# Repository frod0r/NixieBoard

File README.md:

Here I try to recreate the schematics and layout of the nixie clock from this nice instrucables creator:
http://www.instructables.com/id/simple-user-adjustable-DIY-Nixie-Clock/

Please note that I am done BUT I built the clock and it does not work. I have not figured out if it is the components or my plans. I will try to debug it and update here as soon as it works

The reason for me doing so is so that I can generate gerber files with wich I or you can easily order the pcb istead of echtching it oneself :)
If you Andrea Biffi (The creator of the original plans on wich I base my on) want me to remove this respority for a reason, please contact me and I 
will do so.

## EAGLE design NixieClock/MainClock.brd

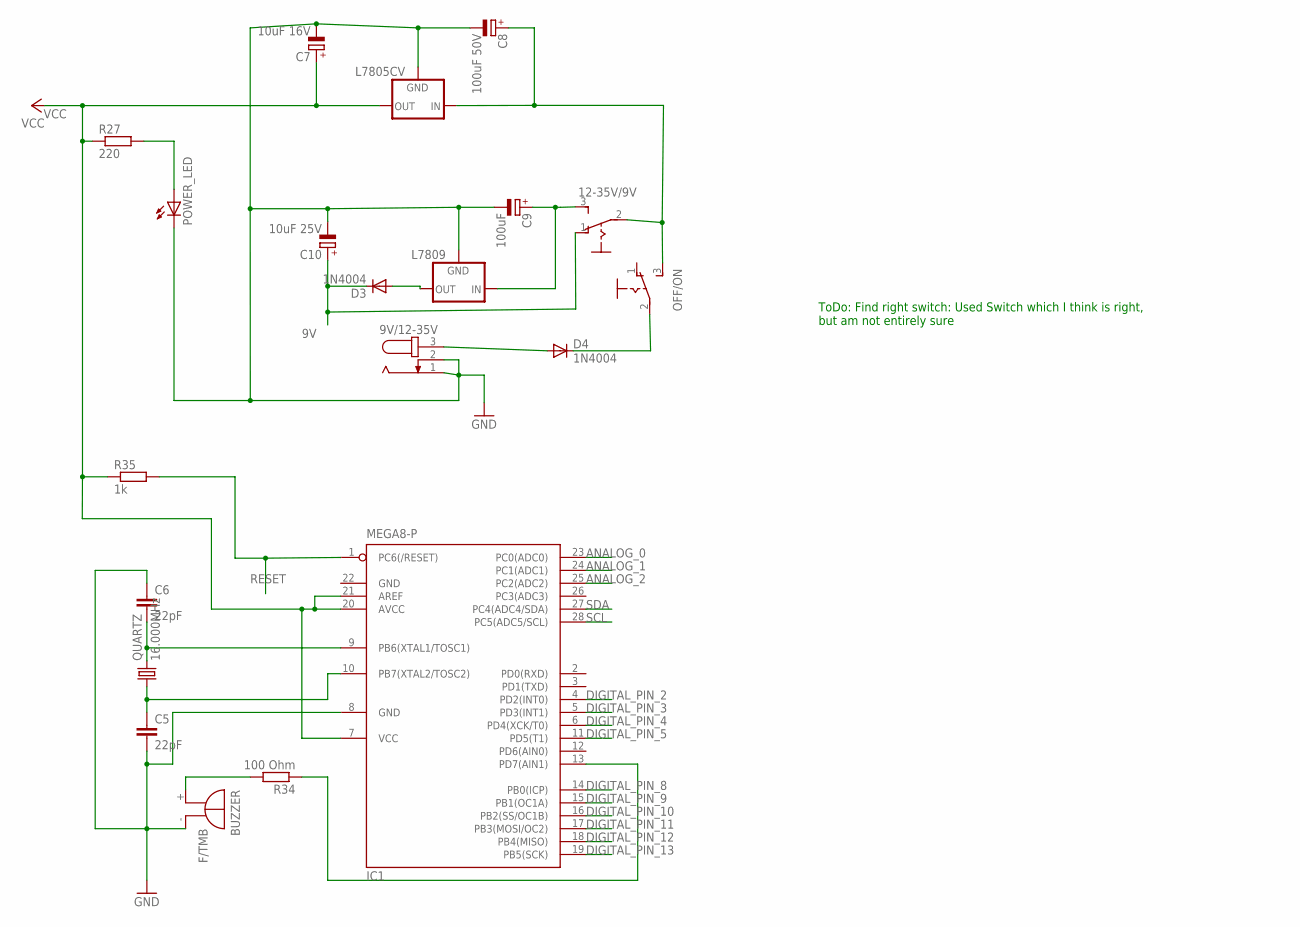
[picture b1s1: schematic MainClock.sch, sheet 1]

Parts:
9V/12-35V: JACK-PLUG1; SPC4078
12-35V/9V: 255SB
BUZZER: F/TMB
C5, C6: 22pF; C025-025X050
C7: 10uF 16V; E5-6
C8: 100uF 50V; E5-8,5
C9: 100uF; E5-8,5
C10: 10uF 25V; E5-6
D3, D4: 1N4004; DO41-10
IC1: MEGA8-P; DIL28-3
L7805CV, L7809: 78XXS
OFF/ON: 255SB
POWER_LED: LED5MM
QUARTZ: 16.000MHz; HC49/S
R27: 220; 0309/10
R34: 100 Ohm; 0411/15
R35: 1k; 0309/10

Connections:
9V: 12-35V/9V.1 (O), C10.+, D3.C; also elsewhere on the board
ANALOG_0: IC1.23 (PC0(ADC0)); also elsewhere on the board
ANALOG_1: IC1.24 (PC1(ADC1)); also elsewhere on the board
ANALOG_2: IC1.25 (PC2(ADC2)); also elsewhere on the board
DIGITAL_PIN_2: IC1.4 (PD2(INT0)); also elsewhere on the board
DIGITAL_PIN_3: IC1.5 (PD3(INT1)); also elsewhere on the board
DIGITAL_PIN_4: IC1.6 (PD4(XCK/T0)); also elsewhere on the board
DIGITAL_PIN_5: IC1.11 (PD5(T1)); also elsewhere on the board
DIGITAL_PIN_8: IC1.14 (PB0(ICP)); also elsewhere on the board
DIGITAL_PIN_9: IC1.15 (PB1(OC1A)); also elsewhere on the board
DIGITAL_PIN_10: IC1.16 (PB2(SS/OC1B)); also elsewhere on the board
DIGITAL_PIN_11: IC1.17 (PB3(MOSI/OC2)); also elsewhere on the board
DIGITAL_PIN_12: IC1.18 (PB4(MISO)); also elsewhere on the board
DIGITAL_PIN_13: IC1.19 (PB5(SCK)); also elsewhere on the board
GND: 9V/12-35V.1, 9V/12-35V.2, BUZZER.-, C5.2, C6.1, C7.-, C8.-, C9.-, C10.-, IC1.8 (GND), IC1.22 (GND), L7805CV.GND, L7809.GND, POWER_LED.K (C); also elsewhere on the board
unnamed: C6.2, IC1.9 (PB6(XTAL1/TOSC1)), QUARTZ.2
unnamed: C5.1, IC1.10 (PB7(XTAL2/TOSC2)), QUARTZ.1
unnamed: BUZZER.+, R34.2
unnamed: IC1.13 (PD7(AIN1)), R34.1
unnamed: 9V/12-35V.3, D4.A
unnamed: D4.C, OFF/ON.2
unnamed: 12-35V/9V.2, C8.+, L7805CV.IN, OFF/ON.3 (S)
unnamed: 12-35V/9V.3 (S), C9.+, L7809.IN
unnamed: POWER_LED.A, R27.2
unnamed: D3.A, L7809.OUT
RESET: IC1.1 (PC6(/RESET)), R35.2; also elsewhere on the board
SCL: IC1.28 (PC5(ADC5/SCL)); also elsewhere on the board
SDA: IC1.27 (PC4(ADC4/SDA)); also elsewhere on the board
VCC: C7.+, IC1.7 (VCC), IC1.20 (AVCC), IC1.21 (AREF), L7805CV.OUT, R27.1, R35.1; also elsewhere on the board

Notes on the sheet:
ToDo: Find right switch: Used Switch which I think is right, but am not entirely sure

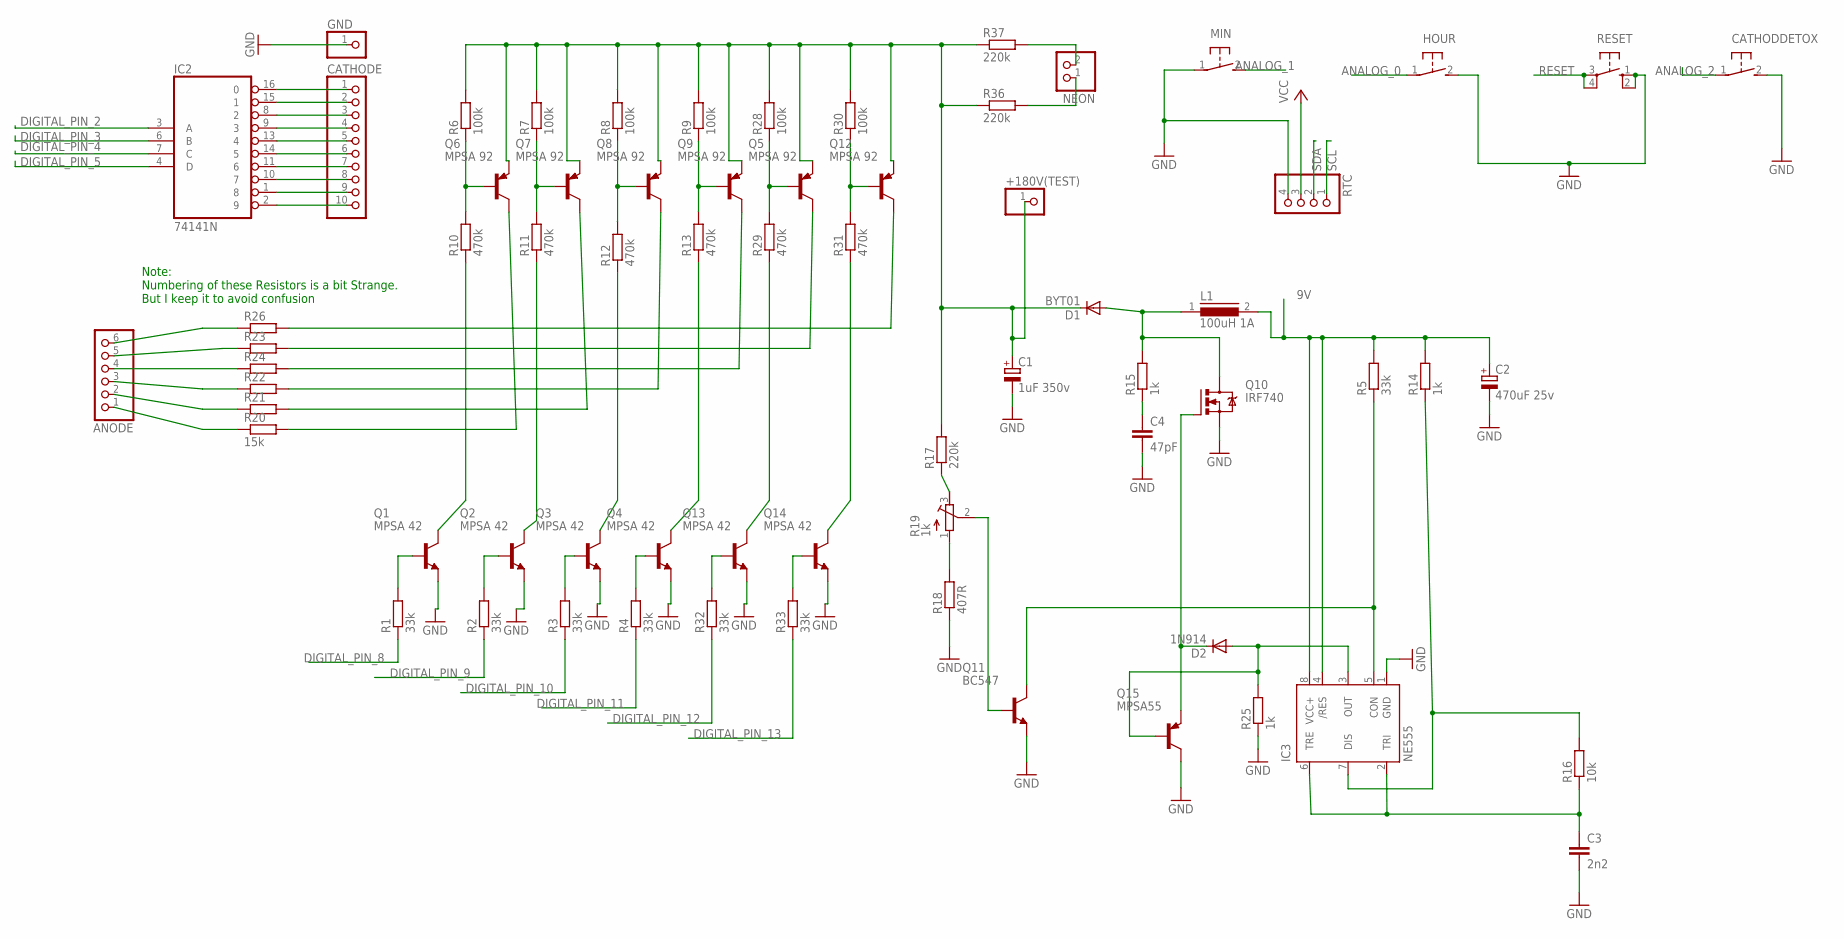
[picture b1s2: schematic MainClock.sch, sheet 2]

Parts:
+180V(TEST): PINHD-1X1; 1X01
ANODE: PINHD-1X6; 1X06
C1: 1uF 350v; E5-10,5
C2: 470uF 25v; E5-10,5
C3: 2n2; C025-024X044
C4: 47pF; C025-024X044
CATHODDETOX: 31-XX; B3F-31XX
CATHODE: PINHD-1X10; 1X10
D1: BYT01; F126-10
D2: 1N914; DO35-10
GND: PINHD-1X1; 1X01
HOUR: 31-XX; B3F-31XX
IC2: 74141N; DIL16
IC3: NE555; DIL-08
L1: 100uH 1A; MESC26
MIN: 31-XX; B3F-31XX
NEON: PINHD-1X2; 1X02
Q1, Q2, Q3, Q4, Q13, Q14: MPSA 42; TO92
Q5, Q6, Q7, Q8, Q9, Q12: MPSA 92; TO92-EBC
Q10: IRF740; TO220BV
Q11: BC547; TO92
Q15: MPSA55; TO92-BCE
R1, R2, R3, R4, R5, R32, R33: 33k; 0309/10
R6, R7, R8, R9, R28, R30: 100k; 0309/10
R10, R11, R12, R13, R29, R31: 470k; 0309/10
R14, R15, R25: 1k; 0309/10
R16: 10k; 0309/10
R17, R36, R37: 220k; 0309/10
R18: 407R; 0309/10
R19: 1k; RTRIM3339P
R20, R21, R22, R23, R24, R26: 15k; 0309/10
RESET: 10-XX; B3F-10XX
RTC: PINHD-1X4; 1X04

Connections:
9V: C2.+, IC3.4 (/RES), IC3.8 (VCC+), L1.2, R5.2, R14.2; also elsewhere on the board
ANALOG_0: HOUR.1; also elsewhere on the board
ANALOG_1: MIN.2 (S); also elsewhere on the board
ANALOG_2: CATHODDETOX.1; also elsewhere on the board
DIGITAL_PIN_2: IC2.3 (A); also elsewhere on the board
DIGITAL_PIN_3: IC2.6 (B); also elsewhere on the board
DIGITAL_PIN_4: IC2.7 (C); also elsewhere on the board
DIGITAL_PIN_5: IC2.4 (D); also elsewhere on the board
DIGITAL_PIN_8: R1.1; also elsewhere on the board
DIGITAL_PIN_9: R2.1; also elsewhere on the board
DIGITAL_PIN_10: R3.1; also elsewhere on the board
DIGITAL_PIN_11: R4.1; also elsewhere on the board
DIGITAL_PIN_12: R32.1; also elsewhere on the board
DIGITAL_PIN_13: R33.1; also elsewhere on the board
GND: C1.-, C2.-, C3.2, C4.2, CATHODDETOX.2 (S), GND.1, HOUR.2 (S), IC2.12 (GND), IC3.1 (GND), MIN.1, Q1.1 (E), Q2.1 (E), Q3.1 (E), Q4.1 (E), Q10.S, Q11.1 (E), Q13.1 (E), Q14.1 (E), Q15.C, R18.1, R25.1, RESET.1 (S), RESET.2 (S1), RTC.4; also elsewhere on the board
unnamed: ANODE.6, R26.1
unnamed: ANODE.5, R23.1
unnamed: ANODE.4, R24.1
unnamed: ANODE.3, R22.1
unnamed: ANODE.2, R21.1
unnamed: ANODE.1, R20.1
unnamed: Q1.2 (B), R1.2
unnamed: Q2.2 (B), R2.2
unnamed: Q13.2 (B), R32.2
unnamed: Q14.2 (B), R33.2
unnamed: Q4.2 (B), R4.2
unnamed: Q3.2 (B), R3.2
unnamed: Q1.3 (C), R10.1
unnamed: Q2.3 (C), R11.1
unnamed: Q3.3 (C), R12.1
unnamed: Q4.3 (C), R13.1
unnamed: Q13.3 (C), R29.1
unnamed: Q14.3 (C), R31.1
unnamed: Q12.B, R30.1, R31.2
unnamed: Q5.B, R28.1, R29.2
unnamed: Q9.B, R9.1, R13.2
unnamed: Q8.B, R8.1, R12.2
unnamed: Q7.B, R7.1, R11.2
unnamed: +180V(TEST).1, C1.+, D1.C, Q5.E, Q6.E, Q7.E, Q8.E, Q9.E, Q12.E, R6.2, R7.2, R8.2, R9.2, R17.2, R28.2, R30.2, R36.1, R37.1
unnamed: Q12.C, R26.2
unnamed: Q5.C, R23.2
unnamed: Q9.C, R24.2
unnamed: Q8.C, R22.2
unnamed: Q7.C, R21.2
unnamed: Q6.C, R20.2
unnamed: CATHODE.1, IC2.16 (0)
unnamed: CATHODE.2, IC2.15 (1)
unnamed: CATHODE.6, IC2.14 (5)
unnamed: CATHODE.5, IC2.13 (4)
unnamed: CATHODE.7, IC2.11 (6)
unnamed: CATHODE.8, IC2.10 (7)
unnamed: CATHODE.4, IC2.9 (3)
unnamed: CATHODE.3, IC2.8 (2)
unnamed: CATHODE.9, IC2.1 (8)
unnamed: CATHODE.10, IC2.2 (9)
unnamed: NEON.1, R36.2
unnamed: NEON.2, R37.2
unnamed: C3.1, IC3.2 (TRI), IC3.6 (TRE), R16.1
unnamed: Q6.B, R6.1, R10.2
unnamed: D1.A, L1.1, Q10.D, R15.2
unnamed: C4.1, R15.1
unnamed: IC3.7 (DIS), R14.1, R16.2
unnamed: IC3.5 (CON), Q11.3 (C), R5.1
unnamed: R18.2, R19.1 (A)
unnamed: R17.1, R19.3 (E)
unnamed: D2.A, IC3.3 (OUT), Q15.B, R25.2
unnamed: D2.C, Q10.G, Q15.E
unnamed: Q11.2 (B), R19.2 (S)
RESET: RESET.3, RESET.4 (P1); also elsewhere on the board
SCL: RTC.1; also elsewhere on the board
SDA: RTC.2; also elsewhere on the board
VCC: IC2.5 (VCC), RTC.3; also elsewhere on the board

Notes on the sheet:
Note: Numbering of these Resistors is a bit Strange. But I keep it to avoid confusion

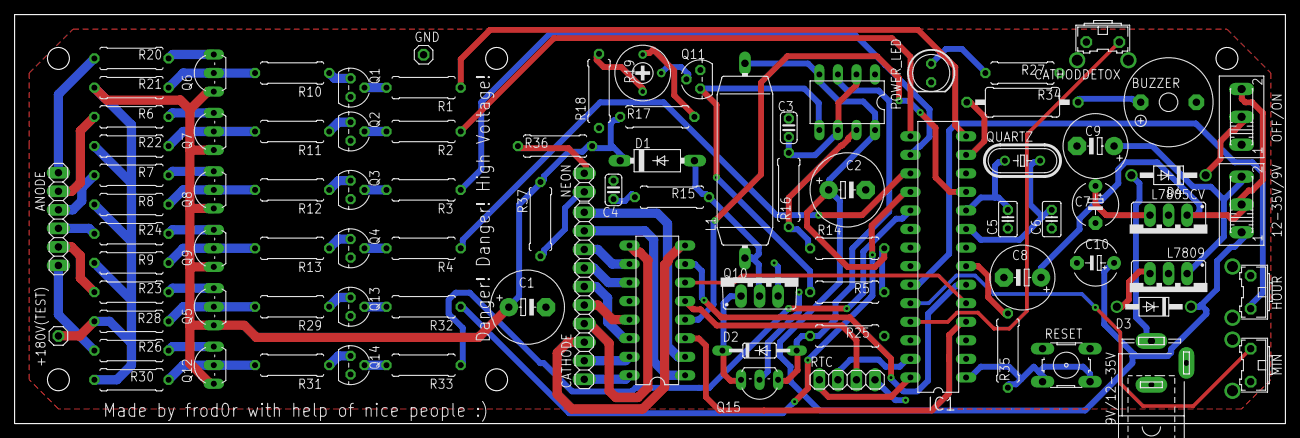
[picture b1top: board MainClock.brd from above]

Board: 2 copper layers, 174.0 x 56.0 mm, 88 parts (0 on the bottom side), 82 nets.

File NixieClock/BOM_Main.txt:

Partlist

Exported from MainClock.brd at 19.04.18 18:20

EAGLE Version 8.7.1 Copyright (c) 1988-2018 Autodesk, Inc.

Assembly variant: 

Part        Value          Package      Library             Position (mm)         Orientation

+180V(TEST)                1X01         pinhead             (6 12)                R0
9V/12-35V                  SPC4078      con-jack            (155.65 8.31)         R90
12-35V/9V                  255SB        switch              (168 30)              R90
ANODE                      1X06         pinhead             (6 28)                R270
BUZZER      F/TMB          F/TMB        buzzer              (158 44)              R180
C1          1uF 350v       E5-10,5      resistor            (70.21 15.94)         R0
C2          470uF 25v      E5-10,5      resistor            (114 32)              R0
C3          2n2            C025-024X044 resistor            (106 40.5)            R90
C4          47pF           C025-024X044 resistor            (82 32)               R90
C5          22pF           C025-025X050 resistor            (136 28)              R270
C6          22pF           C025-025X050 resistor            (142 28)              R90
C7          10uF 16V       E5-6         resistor            (148 30)              R270
C8          100uF 50V      E5-8,5       resistor            (138 20)              R180
C9          100uF          E5-8,5       resistor            (148 38)              R180
C10         10uF 25V       E5-6         resistor            (148 22)              R180
CATHODDETOX                B3F-31XX     switch-omron        (149 51)              R180
CATHODE                    1X10         pinhead             (78 17.5)             R90
D1          BYT01          F126-10      diode               (88 36)               R0
D2          1N914          DO35-10      diode               (102 10)              R0
D3          1N4004         DO41-10      diode               (156 16)              R180
D4          1N4004         DO41-10      diode               (158 34)              R180
GND                        1X01         pinhead             (56 50.5)             R0
HOUR                       B3F-31XX     switch-omron        (168 18)              R90
IC1         MEGA8-P        DIL28-3      atmel               (126.47 22.83)        R90
IC2         74141N         DIL16        74xx-us             (88 15.5)             R90
IC3         NE555          DIL-08       st-microelectronics (114 44)              R180
L1          100uH 1A       MESC26       inductors           (100 36)              R90
L7805CV                    78XXS        v-reg               (158 26)              R180
L7809                      78XXS        v-reg               (158 18)              R180
MIN                        B3F-31XX     switch-omron        (168 8)               R90
NEON                       1X02         pinhead             (78 33)               R270
OFF/ON                     255SB        switch              (168 42)              R90
POWER_LED                  LED5MM       led                 (125.5 48)            R270
Q1          MPSA 42        TO92         transistor          (46 46)               R270
Q2          MPSA 42        TO92         transistor          (46 40)               R270
Q3          MPSA 42        TO92         transistor          (46 32)               R270
Q4          MPSA 42        TO92         transistor          (46 24)               R270
Q5          MPSA 92        TO92-EBC     transistor          (26 16)               R90
Q6          MPSA 92        TO92-EBC     transistor          (26 48)               R90
Q7          MPSA 92        TO92-EBC     transistor          (26 40)               R90
Q8          MPSA 92        TO92-EBC     transistor          (26 32)               R90
Q9          MPSA 92        TO92-EBC     transistor          (26 24)               R90
Q10         IRF740         TO220BV      transistor-power    (102 20)              R0
Q11         BC547          TO92         transistor          (93.89 47.14)         R90
Q12         MPSA 92        TO92-EBC     transistor          (26 8)                R90
Q13         MPSA 42        TO92         transistor          (46 16)               R270
Q14         MPSA 42        TO92         transistor          (46 8)                R270
Q15         MPSA55         TO92-BCE     transistor          (102 6)               R180
QUARTZ      16.000MHz      HC49/S       crystal             (138 36)              R0
R1          33k            0309/10      resistor            (56 46)               R180
R2          33k            0309/10      resistor            (56 40)               R180
R3          33k            0309/10      resistor            (56 32)               R180
R4          33k            0309/10      resistor            (56 24)               R180
R5          33k            0309/10      resistor            (114 18)              R0
R6          100k           0309/10      resistor            (16 46)               R180
R7          100k           0309/10      resistor            (16 38)               R180
R8          100k           0309/10      resistor            (16 30)               R180
R9          100k           0309/10      resistor            (16 22)               R180
R10         470k           0309/10      resistor            (38 48)               R180
R11         470k           0309/10      resistor            (38 40)               R180
R12         470k           0309/10      resistor            (38 32)               R180
R13         470k           0309/10      resistor            (38 24)               R180
R14         1k             0309/10      resistor            (114 24)              R0
R15         1k             0309/10      resistor            (90 31)               R0
R16         10k            0309/10      resistor            (106 32)              R270
R17         220k           0309/10      resistor            (88 42)               R180
R18         407R           0309/10      resistor            (80.02 45.55)         R90
R19         1k             RTRIM3339P   resistor            (86 48)               R90
R20         15k            0309/10      resistor            (16 50)               R0
R21         15k            0309/10      resistor            (16 42)               R0
R22         15k            0309/10      resistor            (16 34)               R0
R23         15k            0309/10      resistor            (16 18)               R0
R24         15k            0309/10      resistor            (16 26)               R0
R25         1k             0309/10      resistor            (114 12)              R180
R26         15k            0309/10      resistor            (16 10)               R0
R27         220            0309/10      resistor            (138 48)              R180
R28         100k           0309/10      resistor            (16 14)               R180
R29         470k           0309/10      resistor            (38 16)               R180
R30         100k           0309/10      resistor            (16 6)                R180
R31         470k           0309/10      resistor            (38 8)                R180
R32         33k            0309/10      resistor            (56 16)               R180
R33         33k            0309/10      resistor            (56 8)                R180
R34         100 Ohm        0411/15      resistor            (138 44)              R0
R35         1k             0309/10      resistor            (136 10)              R270
R36         220k           0309/10      resistor            (74 38)               R180
R37         220k           0309/10      resistor            (72 28)               R270
RESET                      B3F-10XX     switch-omron        (144 8)               R0
RTC                        1X04         pinhead             (114 6)               R0

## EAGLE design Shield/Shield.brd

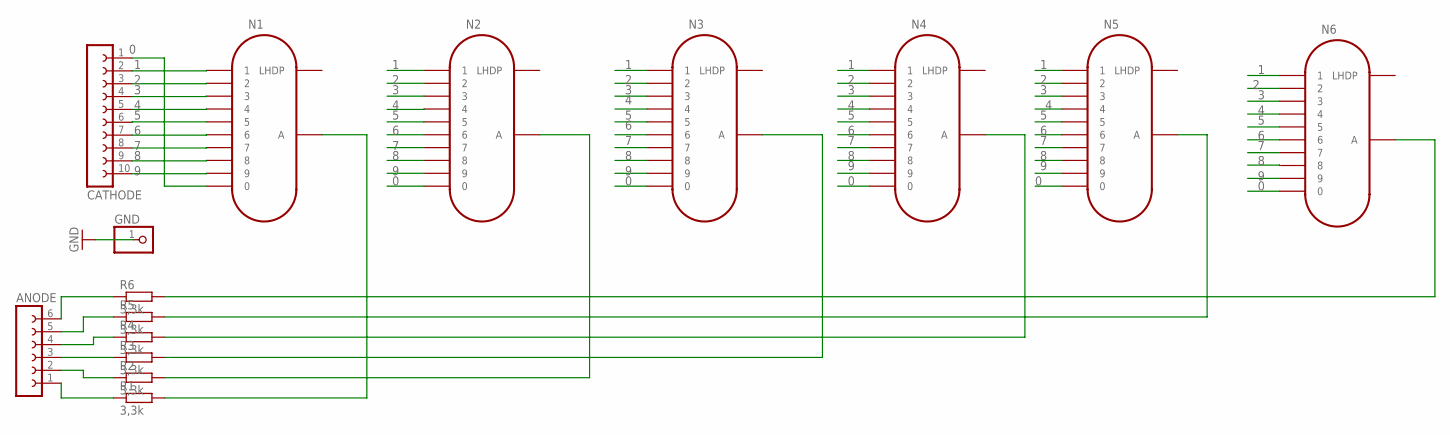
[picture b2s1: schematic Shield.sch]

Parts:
ANODE: FE06-1; FE06
CATHODE: FE10-1; FE10
GND: PINHD-1X1; 1X01
N1, N2, N3, N4, N5, N6: IN-12B; IN-12
R1, R2, R3, R4, R5, R6: 3,3k; 0309/12

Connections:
0: CATHODE.1, N1.0, N2.0, N3.0, N4.0, N5.0, N6.0
1: CATHODE.2, N1.1, N2.1, N3.1, N4.1, N5.1, N6.1
2: CATHODE.3, N1.2, N2.2, N3.2, N4.2, N5.2, N6.2
3: CATHODE.4, N1.3, N2.3, N3.3, N4.3, N5.3, N6.3
4: CATHODE.5, N1.4, N2.4, N3.4, N4.4, N5.4, N6.4
5: CATHODE.6, N1.5, N2.5, N3.5, N4.5, N5.5, N6.5
6: CATHODE.7, N1.6, N2.6, N3.6, N4.6, N5.6, N6.6
7: CATHODE.8, N1.7, N2.7, N3.7, N4.7, N5.7, N6.7
8: CATHODE.9, N1.8, N2.8, N3.8, N4.8, N5.8, N6.8
9: CATHODE.10, N1.9, N2.9, N3.9, N4.9, N5.9, N6.9
GND: GND.1
unnamed: ANODE.1, R1.1
unnamed: ANODE.6, R6.1
unnamed: ANODE.5, R5.1
unnamed: ANODE.2, R2.1
unnamed: ANODE.3, R3.1
unnamed: ANODE.4, R4.1
unnamed: N1.A, R1.2
unnamed: N3.A, R3.2
unnamed: N4.A, R4.2
unnamed: N5.A, R5.2
unnamed: N6.A, R6.2
unnamed: N2.A, R2.2

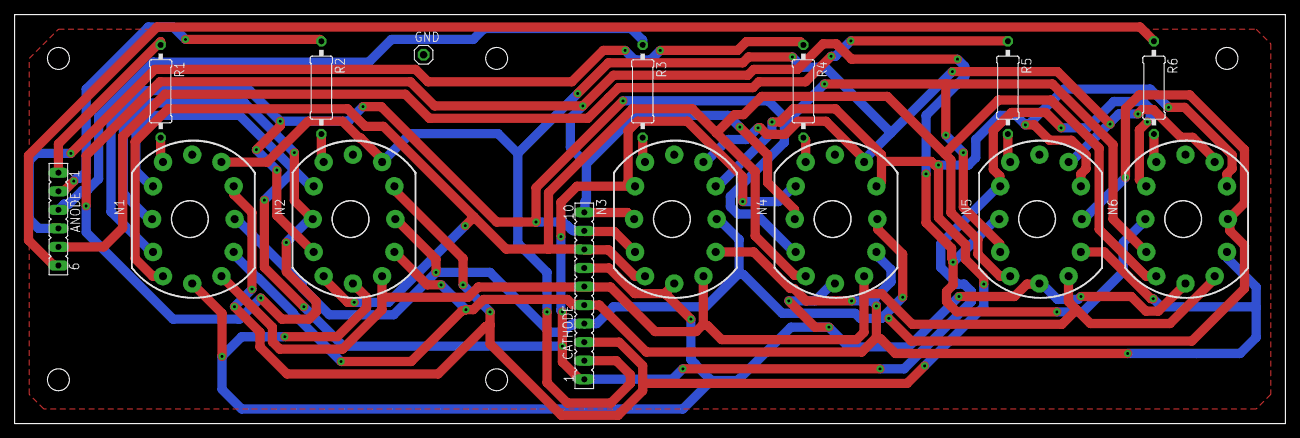
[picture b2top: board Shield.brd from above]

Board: 2 copper layers, 174.0 x 56.0 mm, 15 parts (0 on the bottom side), 22 nets.

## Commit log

2018-03-12 init commit
2018-03-22 Finished first sheet. Declares the 5V as VCC and began second sheet.
2018-03-22 Completed Section A of Sheet 2
2018-03-23 Completed Section B of Sheet 2 and exchanged female heades with pins.
2018-03-31 Finished 2nd Sheet. Still have a few ToDos though
2018-03-31 Resolved ToDOs
2018-03-31 Placed half of the components
2018-03-31 Placed all Parts
2018-03-31 Began Routing
2018-03-31 Routed the rest w the help of autorouter
2018-04-01 Added Holes
2018-04-01 Moved Names and Values so that they are easily readable
2018-04-02 Added a button to the board and added the shield
2018-04-02 spaced routes out
2018-04-03 Trashed old route and ran auto with more spacing
2018-04-03 forgot to save before commit... Comment: See last commit
2018-04-03 applied rules to shield
2018-04-03 applied rules to main
2018-04-19 Added BOM and gitignore files
2018-04-24 Fixed Mistake Some Resistor Labels were swapped. (The Values were at the Right Place)
